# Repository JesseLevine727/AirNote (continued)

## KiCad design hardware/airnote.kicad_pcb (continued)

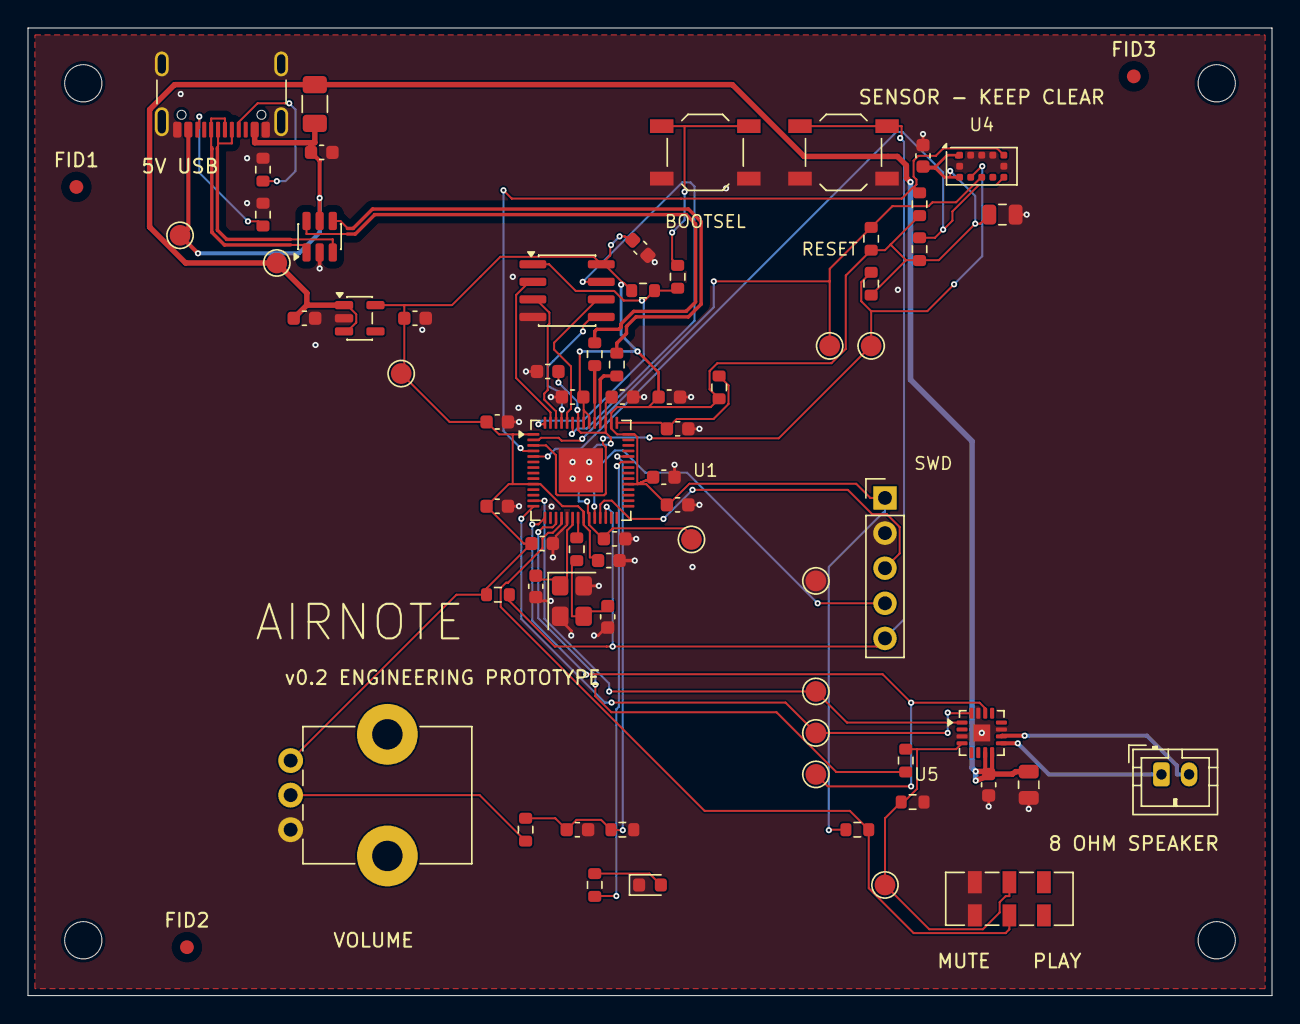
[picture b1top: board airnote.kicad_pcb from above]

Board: 4 copper layers, 90.0 x 70.0 mm, 76 parts (0 on the bottom side), 43 nets.

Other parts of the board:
FID1, FID2, FID3: Fiducial; Fiducial_1mm_Mask2mm
H1, H2, H3, H4: M2.5; MountingHole_2.7mm_M2.5

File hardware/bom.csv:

Reference,Value,Manufacturer,MPN,LCSC,Footprint,Assembly,Notes
U1,RP2040,Raspberry Pi,RP2040,C2040,Package_DFN_QFN:QFN-56-1EP_7x7mm_P0.4mm_EP3.2x3.2mm,Fit,
U2,W25Q16JVSNIQ,Winbond,W25Q16JVSNIQ,C2456211,Package_SO:SOIC-8_3.9x4.9mm_P1.27mm,Fit,Corrected: SN = 150-mil SOIC-8 matching the placed footprint (SS is 208-mil)
Y1,12MHz ABM8-272-T3,Abracon,ABM8-272-T3,C20625731,Crystal:Crystal_SMD_3225-4Pin_3.2x2.5mm,Fit,Listing CL = 10 pF; 15 pF C1/C2 follow the RP2040 minimal reference; verify frequency at bring-up
R1,1k,UNI-ROYAL,0603WAF1001T5E,C21190,Resistor_SMD:R_0603_1608Metric,Fit,
C1,15p,Samsung Electro-Mechanics,CL10C150JB8NNNC,C1644,Capacitor_SMD:C_0603_1608Metric,Fit,
C2,15p,Samsung Electro-Mechanics,CL10C150JB8NNNC,C1644,Capacitor_SMD:C_0603_1608Metric,Fit,
R2,10k,UNI-ROYAL,0603WAF1002T5E,C25804,Resistor_SMD:R_0603_1608Metric,Fit,
R3,1k,UNI-ROYAL,0603WAF1001T5E,C21190,Resistor_SMD:R_0603_1608Metric,Fit,
SW1,BOOTSEL,E-Switch,TL3342F160QG,C2886898,Button_Switch_SMD:SW_SPST_TL3342,Fit,
R4,10k,UNI-ROYAL,0603WAF1002T5E,C25804,Resistor_SMD:R_0603_1608Metric,Fit,
SW2,RESET,E-Switch,TL3342F160QG,C2886898,Button_Switch_SMD:SW_SPST_TL3342,Fit,
J2,SWD 3V3 GND DIO CLK RUN,hanxia,HX PZ2.54-1x5P ZZ,C32713271,Connector_PinHeader_2.54mm:PinHeader_1x05_P2.54mm_Vertical,Fit,Generic 1x5 2.54 mm straight header (straight per LCSC photo); replaces Samtec TSW-105-07-G-S
C3,100n,Yageo,CC0603KRX7R9BB104,C14663,Capacitor_SMD:C_0603_1608Metric,Fit,
C4,100n,Yageo,CC0603KRX7R9BB104,C14663,Capacitor_SMD:C_0603_1608Metric,Fit,
C5,100n,Yageo,CC0603KRX7R9BB104,C14663,Capacitor_SMD:C_0603_1608Metric,Fit,
C6,100n,Yageo,CC0603KRX7R9BB104,C14663,Capacitor_SMD:C_0603_1608Metric,Fit,
C7,100n,Yageo,CC0603KRX7R9BB104,C14663,Capacitor_SMD:C_0603_1608Metric,Fit,
C8,100n,Yageo,CC0603KRX7R9BB104,C14663,Capacitor_SMD:C_0603_1608Metric,Fit,
C9,100n,Yageo,CC0603KRX7R9BB104,C14663,Capacitor_SMD:C_0603_1608Metric,Fit,
C10,100n,Yageo,CC0603KRX7R9BB104,C14663,Capacitor_SMD:C_0603_1608Metric,Fit,
C11,100n,Yageo,CC0603KRX7R9BB104,C14663,Capacitor_SMD:C_0603_1608Metric,Fit,
C12,100n,Yageo,CC0603KRX7R9BB104,C14663,Capacitor_SMD:C_0603_1608Metric,Fit,
C13,1u,Samsung Electro-Mechanics,CL10A105KB8NNNC,C15849,Capacitor_SMD:C_0603_1608Metric,Fit,
C14,1u,Samsung Electro-Mechanics,CL10A105KB8NNNC,C15849,Capacitor_SMD:C_0603_1608Metric,Fit,
C15,100n,Yageo,CC0603KRX7R9BB104,C14663,Capacitor_SMD:C_0603_1608Metric,Fit,
R5,1,UNI-ROYAL,0603WAF100KT5E,C22936,Resistor_SMD:R_0603_1608Metric,Fit,
J1,USB-C USB2.0,GCT,USB4105-GF-A-120,C5184243,AirNote:USB_C_Receptacle_GCT_USB4105-xx-A_16P_TopMnt_Horizontal,Fit,Same land pattern as USB4105-GF-A; 1.20 mm shell stakes
R6,5.1k,UNI-ROYAL,0603WAF5101T5E,C23186,Resistor_SMD:R_0603_1608Metric,Fit,
R7,5.1k,UNI-ROYAL,0603WAF5101T5E,C23186,Resistor_SMD:R_0603_1608Metric,Fit,
D1,USBLC6-2SC6,STMicroelectronics,USBLC6-2SC6,C7519,Package_TO_SOT_SMD:SOT-23-6,Fit,
R8,27,UNI-ROYAL,0603WAF270JT5E,C25190,Resistor_SMD:R_0603_1608Metric,Fit,JLC Extended part
R9,27,UNI-ROYAL,0603WAF270JT5E,C25190,Resistor_SMD:R_0603_1608Metric,Fit,JLC Extended part
F1,500mA hold PTC,Littelfuse,1206L050YR,C163512,Fuse:Fuse_1206_3216Metric,Fit,
U3,AP2112K-3.3,Diodes Inc.,AP2112K-3.3TRG1,C51118,Package_TO_SOT_SMD:SOT-23-5,Fit,
C16,1u,Samsung Electro-Mechanics,CL10A105KB8NNNC,C15849,Capacitor_SMD:C_0603_1608Metric,Fit,
C17,1u,Samsung Electro-Mechanics,CL10A105KB8NNNC,C15849,Capacitor_SMD:C_0603_1608Metric,Fit,
C18,100n,Yageo,CC0603KRX7R9BB104,C14663,Capacitor_SMD:C_0603_1608Metric,Fit,
U4,VL53L1CXV0FY/1,STMicroelectronics,VL53L1CXV0FY/1,C190004,Sensor_Distance:ST_VL53L1x,Fit,
C19,100n,Yageo,CC0603KRX7R9BB104,C14663,Capacitor_SMD:C_0603_1608Metric,Fit,
C20,4.7u,Samsung Electro-Mechanics,CL21A475KAQNNNE,C1779,Capacitor_SMD:C_0805_2012Metric,Fit,
R10,10k,UNI-ROYAL,0603WAF1002T5E,C25804,Resistor_SMD:R_0603_1608Metric,Fit,
R11,10k,UNI-ROYAL,0603WAF1002T5E,C25804,Resistor_SMD:R_0603_1608Metric,Fit,
R12,5.1k,UNI-ROYAL,0603WAF5101T5E,C23186,Resistor_SMD:R_0603_1608Metric,Fit,
R13,5.1k,UNI-ROYAL,0603WAF5101T5E,C23186,Resistor_SMD:R_0603_1608Metric,Fit,
U5,MAX98357AETE+T,Analog Devices,MAX98357AETE+T,C910544,AirNote:MAX98357A_T1633_ADI_90-0031,Fit,
C21,100n,Yageo,CC0603KRX7R9BB104,C14663,Capacitor_SMD:C_0603_1608Metric,Fit,
C22,4.7u,Samsung Electro-Mechanics,CL21A475KAQNNNE,C1779,Capacitor_SMD:C_0805_2012Metric,Fit,
J3,SPEAKER 8ohm >=1W,JST,B2B-PH-K-S(LF)(SN),C131337,Connector_JST:JST_PH_B2B-PH-K_1x02_P2.00mm_Vertical,Fit,
R14,10k,UNI-ROYAL,0603WAF1002T5E,C25804,Resistor_SMD:R_0603_1608Metric,Fit,
R15,100k,UNI-ROYAL,0603WAF1003T5E,C25803,Resistor_SMD:R_0603_1608Metric,Fit,
R16,10k,UNI-ROYAL,0603WAF1002T5E,C25804,Resistor_SMD:R_0603_1608Metric,Fit,
SW3,MUTE / PLAY,C&K,JS202011JCQN,C221665,Button_Switch_SMD:SW_DPDT_CK_JS202011JCQN,Fit,
RV1,10k LINEAR VOLUME,Bourns,PTV09A-4015F-B103,C5710902,Potentiometer_THT:Potentiometer_Bourns_PTV09A-1_Single_Vertical,Fit,"Bushingless, 15 mm flat shaft; same PTV09 rear-mount land pattern as -1020F; knob sits about 5 mm lower"
R17,1k,UNI-ROYAL,0603WAF1001T5E,C21190,Resistor_SMD:R_0603_1608Metric,Fit,
C23,100n,Yageo,CC0603KRX7R9BB104,C14663,Capacitor_SMD:C_0603_1608Metric,Fit,
D2,GREEN STATUS,Lite-On,LTST-C190KGKT,C125094,LED_SMD:LED_0603_1608Metric,Fit,Listed colour yellow-green (574 nm)
R18,1k,UNI-ROYAL,0603WAF1001T5E,C21190,Resistor_SMD:R_0603_1608Metric,Fit,
R19,1M,UNI-ROYAL,0603WAF1004T5E,C22935,Resistor_SMD:R_0603_1608Metric,Fit,
TP1,VBUS_RAW,,TEST_PAD_1.5MM,,TestPoint:TestPoint_Pad_D1.5mm,PCB only,Bare PCB pad; no fitted component
TP2,+5V,,TEST_PAD_1.5MM,,TestPoint:TestPoint_Pad_D1.5mm,PCB only,Bare PCB pad; no fitted component
TP3,+3V3,,TEST_PAD_1.5MM,,TestPoint:TestPoint_Pad_D1.5mm,PCB only,Bare PCB pad; no fitted component
TP4,+1V1,,TEST_PAD_1.5MM,,TestPoint:TestPoint_Pad_D1.5mm,PCB only,Bare PCB pad; no fitted component
TP5,GND,,TEST_PAD_1.5MM,,TestPoint:TestPoint_Pad_D1.5mm,PCB only,Bare PCB pad; no fitted component
TP6,I2C_SDA,,TEST_PAD_1.5MM,,TestPoint:TestPoint_Pad_D1.5mm,PCB only,Bare PCB pad; no fitted component
TP7,I2C_SCL,,TEST_PAD_1.5MM,,TestPoint:TestPoint_Pad_D1.5mm,PCB only,Bare PCB pad; no fitted component
TP8,I2S_DATA,,TEST_PAD_1.5MM,,TestPoint:TestPoint_Pad_D1.5mm,PCB only,Bare PCB pad; no fitted component
TP9,I2S_BCLK,,TEST_PAD_1.5MM,,TestPoint:TestPoint_Pad_D1.5mm,PCB only,Bare PCB pad; no fitted component
TP10,I2S_LRCLK,,TEST_PAD_1.5MM,,TestPoint:TestPoint_Pad_D1.5mm,PCB only,Bare PCB pad; no fitted component
TP11,AMP_SD,,TEST_PAD_1.5MM,,TestPoint:TestPoint_Pad_D1.5mm,PCB only,Bare PCB pad; no fitted component

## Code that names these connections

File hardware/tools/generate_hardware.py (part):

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add('U1','MCU_RaspberryPi:RP2040','RP2040','Package_DFN_QFN:QFN-56-1EP_7x7mm_P0.4mm_EP3.2x3.2mm','RP2040',cn,'core',(81.28,96.52),(90,82),manufacturer='Raspberry Pi')
add('U2','Memory_Flash:W25Q16JVSS','W25Q16JVSSIQ','Package_SO:SOIC-8_3.9x4.9mm_P1.27mm','W25Q16JVSSIQ',{1:'QSPI_CS',6:'QSPI_CLK',5:'QSPI_D0',2:'QSPI_D1',3:'QSPI_D2',7:'QSPI_D3',8:'+3V3',4:'GND'},'core',(190.5,58.42),(89,69),manufacturer='Winbond')
add('Y1','Device:Crystal_GND24','12MHz ABM8-272-T3','Crystal:Crystal_SMD_3225-4Pin_3.2x2.5mm','ABM8-272-T3',{1:'XIN',3:'XTAL_OUT',2:'GND',4:'GND'},'core',(193.04,116.84),(92,91),manufacturer='Abracon')
resistor('1k','XOUT','XTAL_OUT','core',(203.2,142.24),(89,90),90)
cap('15p','XIN','GND','core',(172.72,116.84),(89,93),0)
cap('15p','XTAL_OUT','GND','core',(218.44,116.84),(95,93),0)
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add('SW1','Switch:SW_Push','BOOTSEL','Button_Switch_SMD:SW_SPST_TL3342','TL3342F160QG',{1:'BOOTSEL_SW',2:'GND'},'core',(269.24,58.42),(99,59),manufacturer='E-Switch')
resistor('10k','+3V3','RUN','core',(243.84,93.98),(84,91),0)
add('SW2','Switch:SW_Push','RESET','Button_Switch_SMD:SW_SPST_TL3342','TL3342F160QG',{1:'RUN',2:'GND'},'core',(269.24,93.98),(109,59),manufacturer='E-Switch')
add('J2','Connector_Generic:Conn_01x05','SWD 3V3 GND DIO CLK RUN','Connector_PinHeader_2.54mm:PinHeader_1x05_P2.54mm_Vertical','TSW-105-07-G-S',{1:'+3V3',2:'GND',3:'SWDIO',4:'SWCLK',5:'RUN'},'core',(304.8,132.08),(112,84),manufacturer='Samtec')
# Every RP2040 supply pin has local decoupling.
for i,(xy,net) in enumerate([((85.2,78),'+3V3'),((85.2,84.6),'+3V3'),((87.2,86.8),'+3V3'),((93.6,86.8),'+3V3'),((94.8,82),'+3V3'),((94.8,77.2),'+3V3'),((92.8,76.6),'+3V3'),((87,77),'+1V1'),((94.4,74.6),'+1V1'),((97,79),'ADC_3V3')]):
 cap('100n',net,'GND','core',(48.26+27.94*(i%5),177.8+38.1*(i//5)),xy,0)
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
